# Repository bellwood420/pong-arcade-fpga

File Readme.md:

# Arcade Pong(1972) on FPGA
Original arcade version Pong(1972) by Atari implemented on FPGA with external analog circuit. 

# Features

## 1. Synchronous drive

The original circuit consists of so many asynchronous aspects, causing unstability both in routing and running on FPGA.  

To avoid it, I implemented whole circuit synchronously by treating clock signals to registers as datapaths for edge detection,
and driving them by main clock.  

This technique is introduced in the [Reference 1](#References)

## 2. Real paddle input

LMC555 and potentiometer on external circuit provide realistic paddle experience.  

Conversely, you cannnot play without them...😇

## 3. Analog video & sound output

RCA connectors on external circuit output NTSC spec video signal and line level sound signal.  

It would be nice to output video signal from VGA connector on typical FPGA boards, but I'm not good enough to make upscaler. 

# Requirements

## External analog circuit
**You need external analog circuit** other than FPGA board to play the game.
- Schematic availabe: pcb/ext-board/ext-board.pdf
- PCB gerber files available: pcb/ext-board/gerber/
- You can build it on breadboard, universal board or use my PCB.
- PCB has 40-pins GPIO connector for Terasic FPGA boards and 12-pins Pmod connector for Digilent FPGA boards.

## FPGA board

Example project files available for the boards below:

<table>
  <tr>
    <th align="left">Board</th>
    <th align="left">Terasic<br>DE0-CV</th>
    <th align="left">Terasic<br>DE-10 Nano</th>
    <th align="left">Digilent<br>Nexys4 DDR</th>
    <th></th>
  </tr>
  <tr>
    <td>Chip</td>
    <td colspan="2">Intel/Altera Cyclone V</td>
    <td>Xilinx Artix-7</td>
    <td></td>
  </tr>
  <tr>
    <td>IDE version</td>
    <td colspan="2">Quartus Prime Lite Edition 20.1</td>
    <td>Vivado 2020.1</td>
    <td></td>
  </tr>
  <tr>
    <td>Start button<br>(COIN_SW)</td>
    <td colspan="2">KEY0</td>
    <td>BTNC</td>
    <td></td>
  </tr>
  <tr>
    <td>Max point sel<br>(SW1A/SW1B)</td>
    <td colspan="3">SW[0]/SW[1]</td>
    <td>On: 15 pts, Off 11 pts</td>
  </tr>
  <tr>
    <td>Connector</td>
    <td>GPIO1</td>
    <td>GPIO0</td>
    <td>Pmod A</td>
    <td>See schematics or qsf/xdc for details</td>
  </tr>
</table>

# References
Without the following documents, I would not have been able to finish this project and understand the mystery of a video game built only on discrete logic ICs. 

1. Stephen A. Edwards. Reconstructing Pong on an FPGA. 2012.  
  http://www.cs.columbia.edu/~sedwards/papers/edwards2012reconstructing.pdf
2. Hugo R. Holden. ATARI PONG E CIRCUIT ANALYSIS & LAWN TENNIS: BUILDING A DIGITAL VIDEO GAME WITH 74 SERIES TTL IC’s. 2013.  
  http://worldphaco.com/uploads/LAWN_TENNIS.pdf

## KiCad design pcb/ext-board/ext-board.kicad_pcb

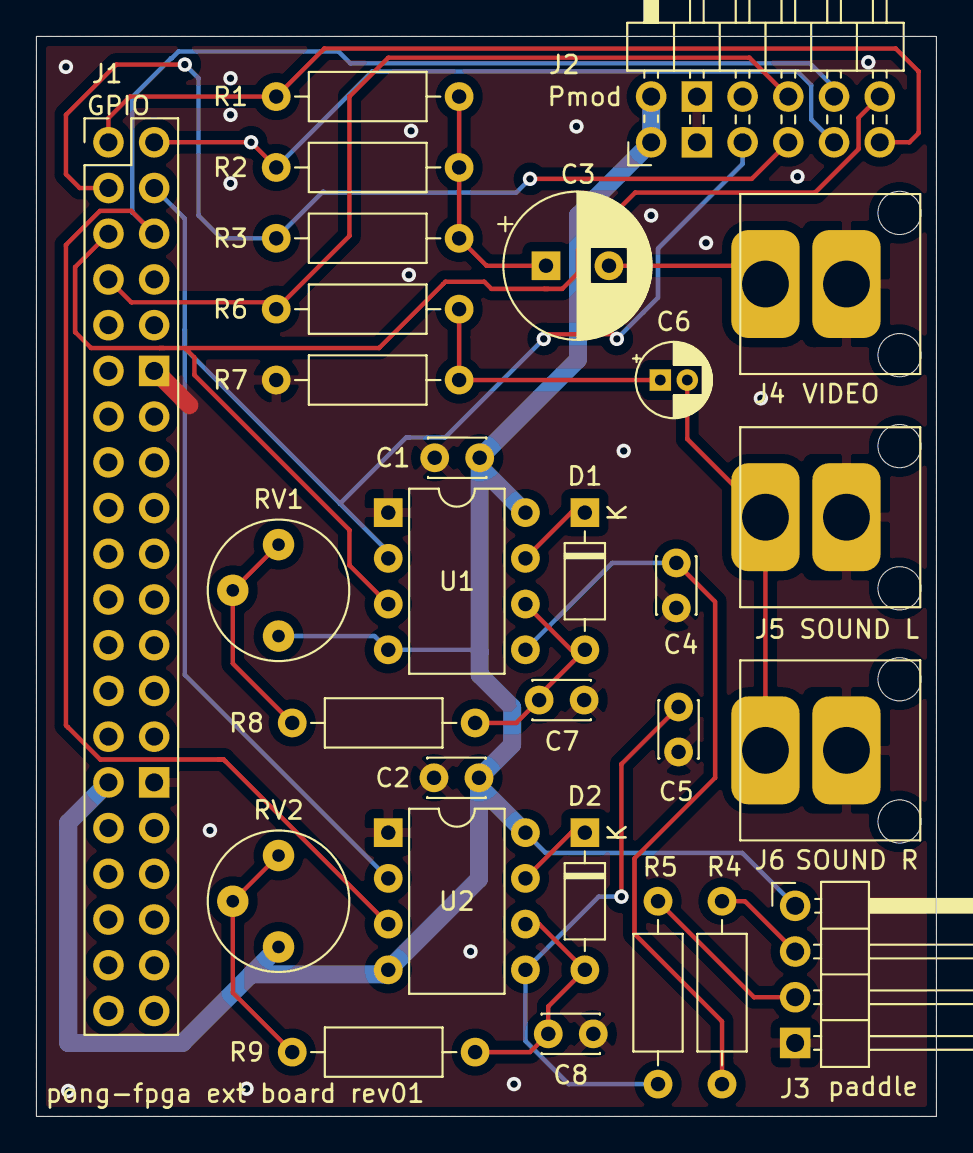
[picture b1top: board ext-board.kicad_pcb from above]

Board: 2 copper layers, 50.0 x 60.0 mm, 29 parts (0 on the bottom side), 23 nets.

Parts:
C1, C2, C4, C5, C7, C8: 0.1u; C_Disc_D3.0mm_W2.0mm_P2.50mm
C3: 470u; CP_Radial_D8.0mm_P3.50mm
C6: 10u; CP_Radial_D4.0mm_P1.50mm
D1, D2: 1N4148; D_DO-35_SOD27_P7.62mm_Horizontal
J1: DE GPIO; PinHeader_2x20_P2.54mm_Vertical
J2: Digilent Pmod; PmodConnector
J3: PADDLE CONNECTOR; PinHeader_1x04_P2.54mm_Horizontal
J4: VIDEO OUT; RJ-2410N
J5: SOUND L OUT; RJ-2410N
J6: SOUND R OUT; RJ-2410N
R1, R4, R5: 470; R_Axial_DIN0207_L6.3mm_D2.5mm_P10.16mm_Horizontal
R2: 180; R_Axial_DIN0207_L6.3mm_D2.5mm_P10.16mm_Horizontal
R3: 220; R_Axial_DIN0207_L6.3mm_D2.5mm_P10.16mm_Horizontal
R6: 47k; R_Axial_DIN0207_L6.3mm_D2.5mm_P10.16mm_Horizontal
R7: 4.7k; R_Axial_DIN0207_L6.3mm_D2.5mm_P10.16mm_Horizontal
R8, R9: 56k; R_Axial_DIN0207_L6.3mm_D2.5mm_P10.16mm_Horizontal
RV1, RV2: 50k; Potentiometer_Bourns_3339P_Vertical_HandSoldering
U1, U2: LMC555xN; DIP-8_W7.62mm

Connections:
+3V3: C1.2, C2.2, J1.29, J2.6, J2.12, J3.1, RV1.1, RV2.1, U1.4, U1.8, U2.4, U2.8
/CSYNC: J1.1, J2.1, R1.2
/PAD1: J3.2, R4.2
/PAD1_OUT: J1.5, J2.7, U1.3
/PAD2: J3.3, R5.2
/PAD2_OUT: J1.6, J2.8, U2.3
/PAD_TRG_N: J1.4, J2.4, U1.2, U2.2
/SCORE: J1.3, J2.3, R3.2
/SOUND: J1.7, J2.9, R6.2
/VIDEO: J1.2, J2.2, R2.2
GND: C1.1, C2.1, C4.2, C5.2, C7.2, C8.2, J1.12, J1.30, J2.5, J2.11, J3.4, J4.2, J5.2, J6.2, R7.2, U1.1, U2.1
unnamed: C3.1, R1.1, R2.1, R3.1
unnamed: C3.2, J4.1
unnamed: C4.1, R4.1, U1.5
unnamed: C5.1, R5.1, U2.5
unnamed: C6.1, R6.1, R7.1
unnamed: C6.2, J5.1, J6.1
unnamed: C7.1, D1.2, R8.2, U1.6
unnamed: C8.1, D2.2, R9.2, U2.6
unnamed: D1.1, U1.7
unnamed: D2.1, U2.7
unnamed: R8.1, RV1.2, RV1.3
unnamed: R9.1, RV2.2, RV2.3

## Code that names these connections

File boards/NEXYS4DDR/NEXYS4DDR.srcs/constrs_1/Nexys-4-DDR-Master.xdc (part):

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
##Pmod Header JA

set_property -dict { PACKAGE_PIN C17   IOSTANDARD LVCMOS33 } [get_ports { CSYNC }]; #IO_L20N_T3_A19_15 Sch=ja[1]
set_property -dict { PACKAGE_PIN D18   IOSTANDARD LVCMOS33 } [get_ports { VIDEO }]; #IO_L21N_T3_DQS_A18_15 Sch=ja[2]
set_property -dict { PACKAGE_PIN E18   IOSTANDARD LVCMOS33 } [get_ports { SCORE }]; #IO_L21P_T3_DQS_15 Sch=ja[3]
set_property -dict { PACKAGE_PIN G17   IOSTANDARD LVCMOS33 } [get_ports { PAD_TRG_N }]; #IO_L18N_T2_A23_15 Sch=ja[4]
set_property -dict { PACKAGE_PIN D17   IOSTANDARD LVCMOS33 } [get_ports { PAD1_OUT }]; #IO_L16N_T2_A27_15 Sch=ja[7]
set_property -dict { PACKAGE_PIN E17   IOSTANDARD LVCMOS33 } [get_ports { PAD2_OUT }]; #IO_L16P_T2_A28_15 Sch=ja[8]
set_property -dict { PACKAGE_PIN F18   IOSTANDARD LVCMOS33 } [get_ports { SOUND }]; #IO_L22N_T3_A16_15 Sch=ja[9]
#set_property -dict { PACKAGE_PIN G18   IOSTANDARD LVCMOS33 } [get_ports { JA[7] }]; #IO_L22P_T3_A17_15 Sch=ja[10]


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
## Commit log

2020-11-15 Update Readme.md
    Added missing information
2020-11-15 Update Readme.md
    Organized in a table
2020-11-15 Update Readme.md
    Added line breaks for readability
2020-11-26 Deleted unnecessary file
2020-11-26 Added project files for DE10-NANO
2020-11-26 Update Readme.md
    Added description for Terasic DE-10 Nano
2020-11-28 Update Readme.md
    Fixed incorrect use of word
